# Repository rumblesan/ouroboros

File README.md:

# Ouroboros

A noisy feedback system

## Description

A pinged filter feeds a PT delay, which feeds a comparator, which feeds some clock dividers, which pings the filter and modulate the rest of the system

## Contact

Drop me an email at guy@rumblesan.com

## License

This work is licensed under a [Creative Commons Attribution 4.0 International License]("http://creativecommons.org/licenses/by/4.0/")

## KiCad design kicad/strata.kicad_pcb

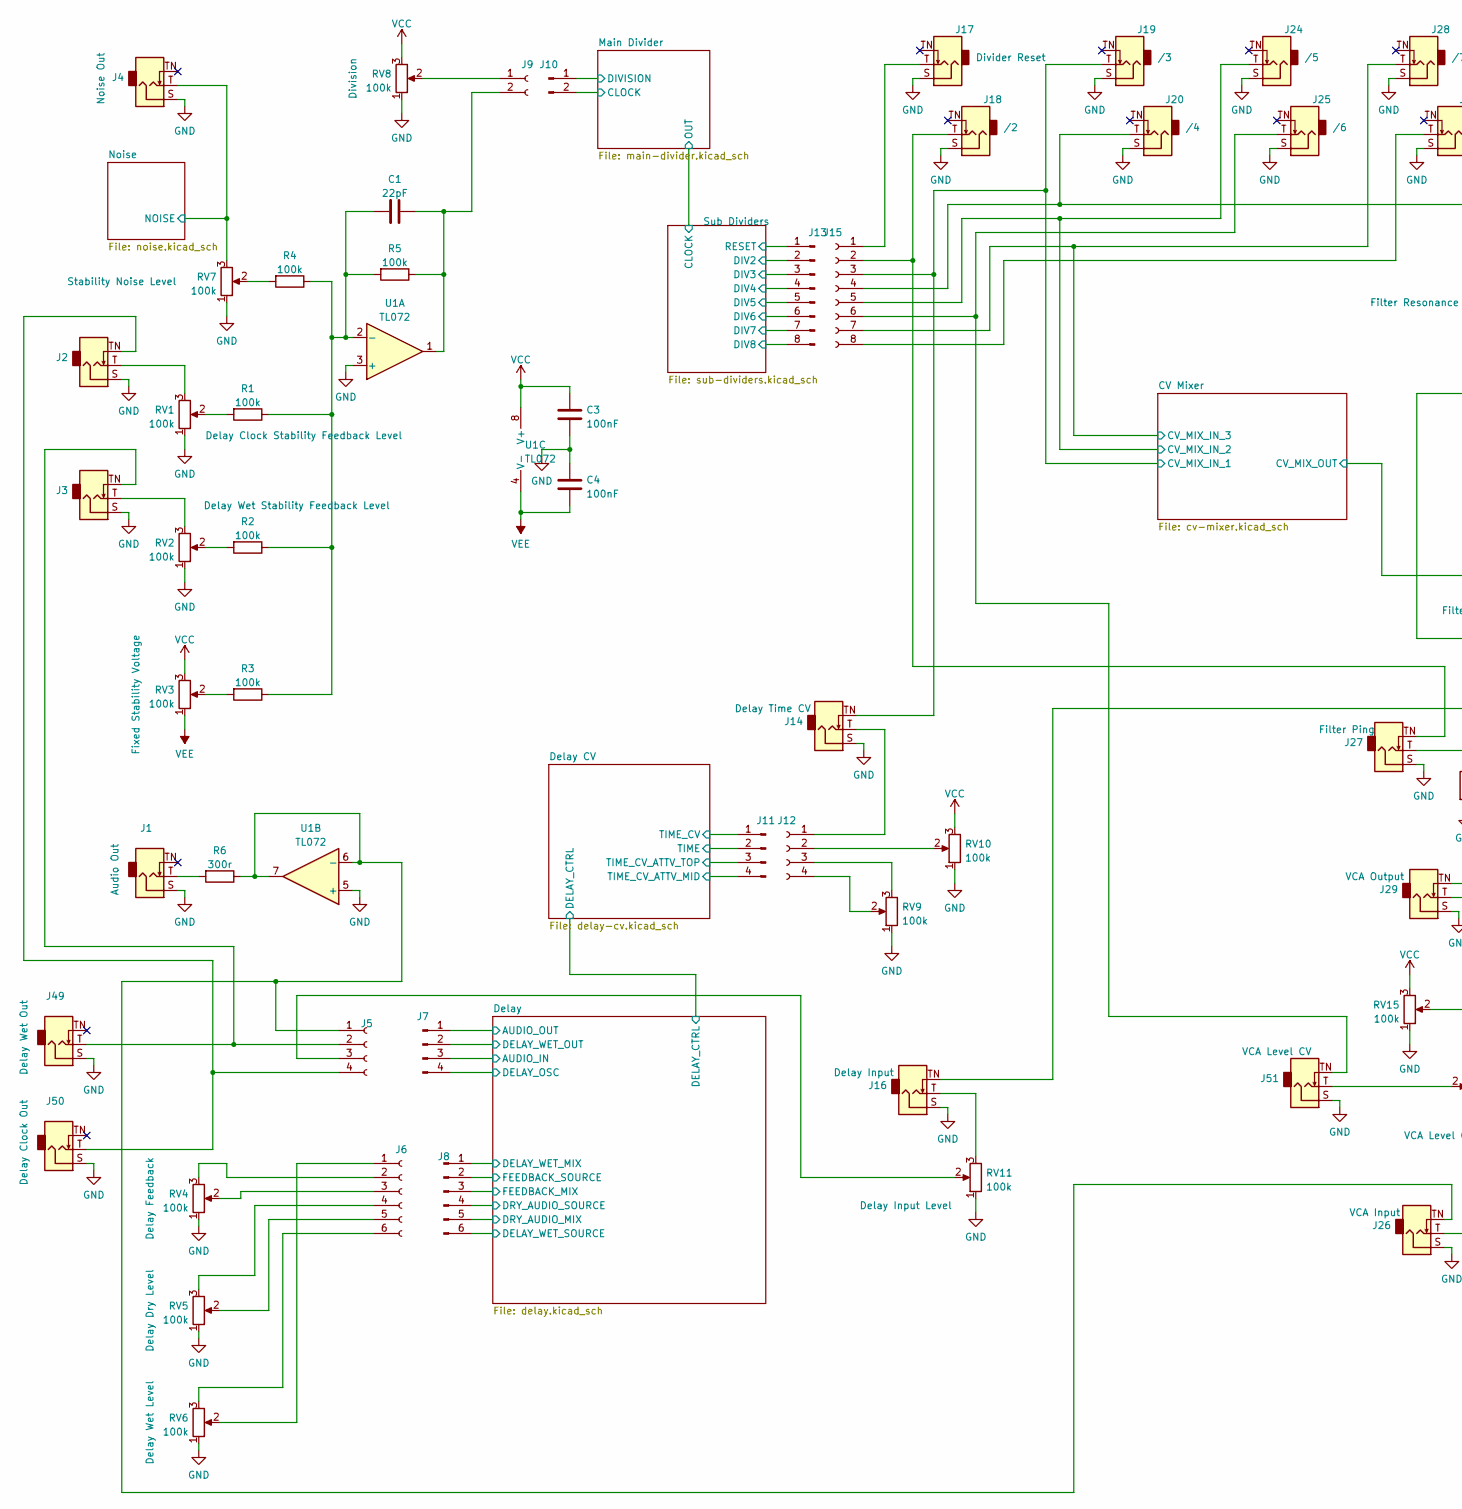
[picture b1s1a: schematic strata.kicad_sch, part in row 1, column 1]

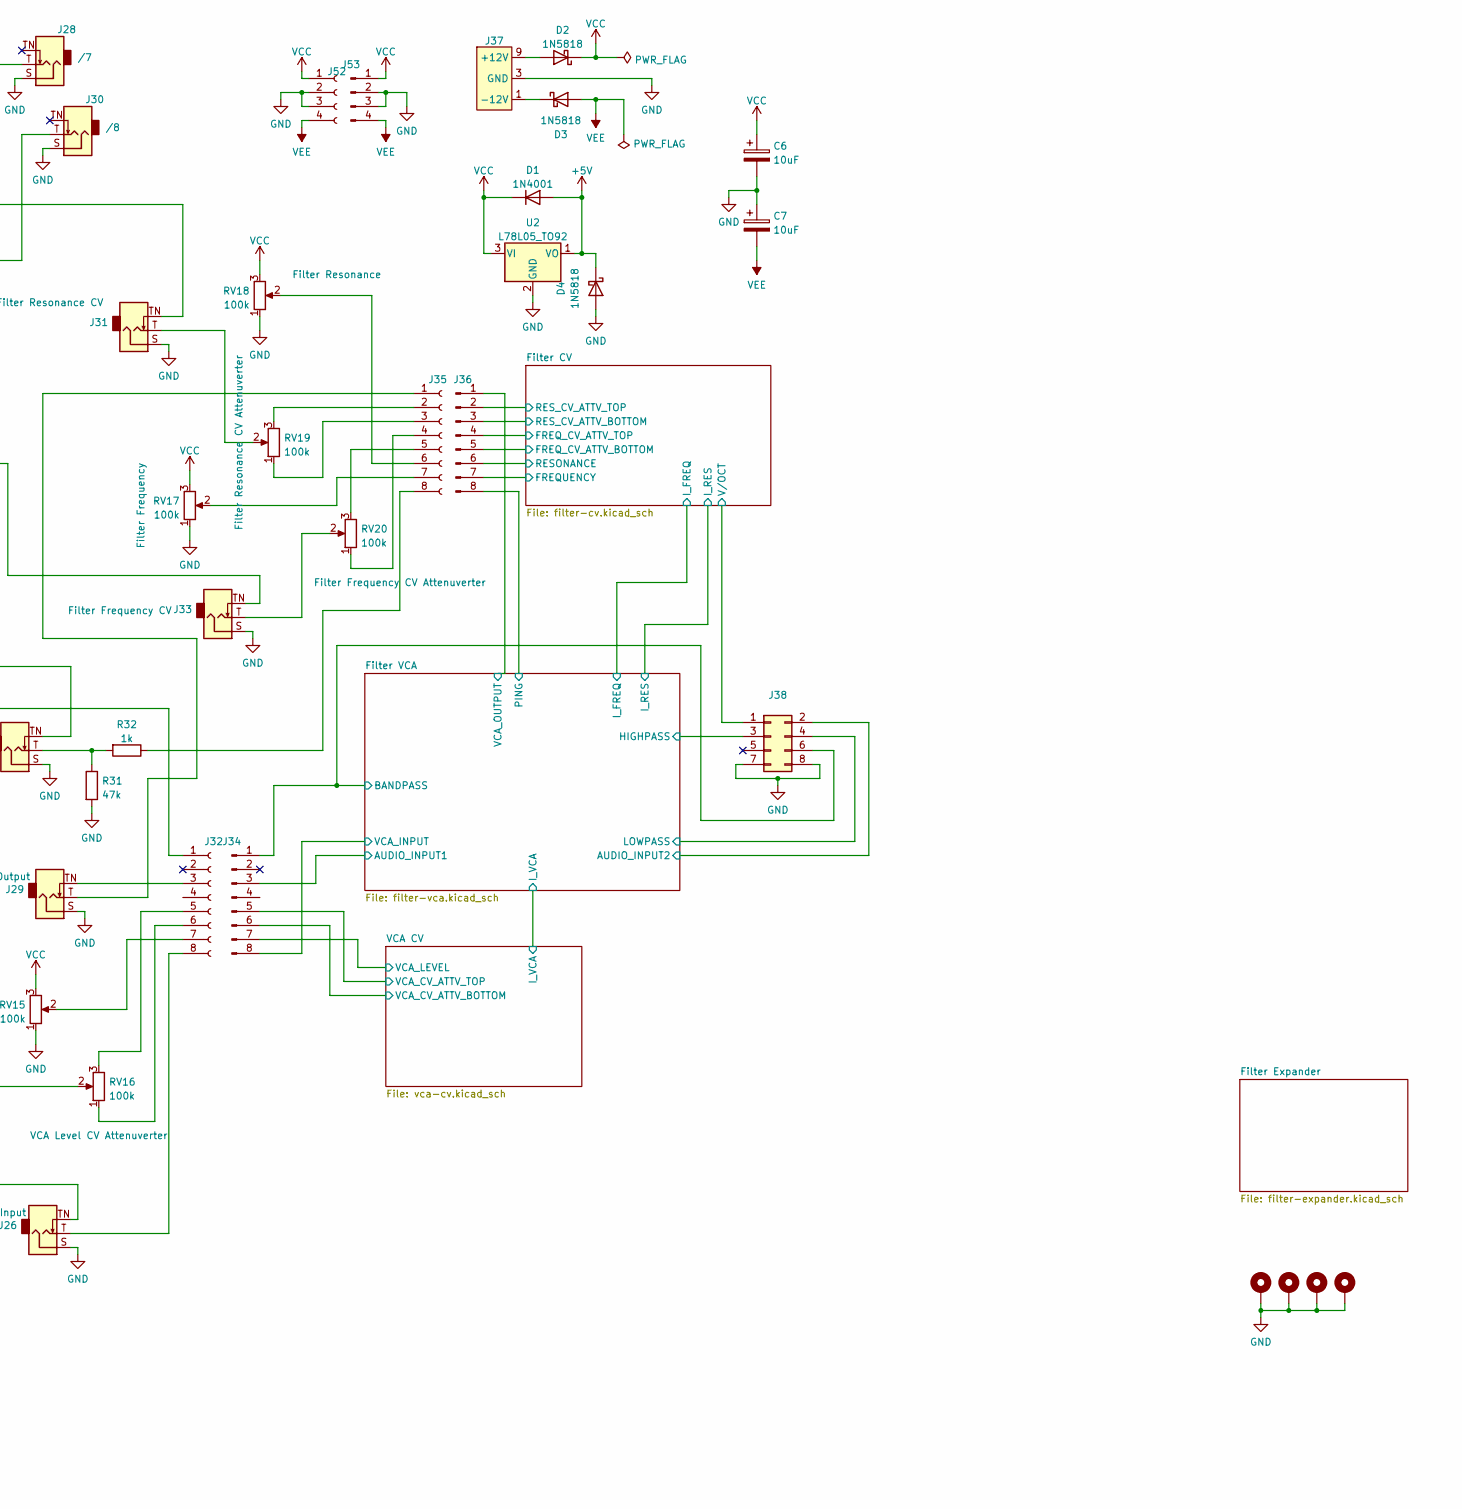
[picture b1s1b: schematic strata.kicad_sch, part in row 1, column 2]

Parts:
C1: 22pF; C_Rect_L7.0mm_W2.5mm_P5.00mm; Tolerance 5%
C3, C4: 100nF; C_Rect_L7.0mm_W2.5mm_P5.00mm; Tolerance 5%
C6, C7: 10uF; CP_Radial_D5.0mm_P2.00mm; Tolerance 20%; Voltage 50v
D1: 1N4001; D_DO-41_SOD81_P10.16mm_Horizontal
D2, D3, D4: 1N5818; D_DO-41_SOD81_P10.16mm_Horizontal
H1, H2, H3, H4: MountingHole_Pad; MountingHole_3.2mm_M3_DIN965_Pad
J1, J2, J3, J4, J14, J16, J17, J18, J19, J20, J24, J25, J26, J27, J28, J29, J30, J31, J33, J49, J50, J51: Eurorack Mono Jack; Jack_3.5mm_QingPu_WQP-PJ398SM_Vertical; mpn WQP-WQP518MA
J5, J12, J52: Conn_01x04_Female; PinSocket_1x04_P2.54mm_Vertical
J6: Conn_01x06_Female; PinSocket_1x06_P2.54mm_Vertical
J7, J11, J53: Conn_01x04_Male; PinHeader_1x04_P2.54mm_Vertical
J8: Conn_01x06_Male; PinHeader_1x06_P2.54mm_Vertical
J9: Conn_01x02_Female; PinSocket_1x02_P2.54mm_Vertical
J10: Conn_01x02_Male; PinHeader_1x02_P2.54mm_Vertical
J13, J34, J36: Conn_01x08_Male; PinHeader_1x08_P2.54mm_Vertical
J15, J32, J35: Conn_01x08_Female; PinSocket_1x08_P2.54mm_Vertical
J37: Eurorack Power Small; Eurorack_PowerHeader_2x05_P2.54mm_Shrouded
J38: Conn_02x04_Odd_Even; PinHeader_2x04_P2.54mm_Vertical
R1, R2, R3, R4, R5: 100k; R_Axial_DIN0207_L6.3mm_D2.5mm_P10.16mm_Horizontal; Tolerance 1%
R6: 300r; R_Axial_DIN0207_L6.3mm_D2.5mm_P10.16mm_Horizontal; Tolerance 1%
R31: 47k; R_Axial_DIN0207_L6.3mm_D2.5mm_P10.16mm_Horizontal; Tolerance 1%
R32: 1k; R_Axial_DIN0207_L6.3mm_D2.5mm_P10.16mm_Horizontal; Tolerance 1%
RV1, RV2, RV3, RV4, RV5, RV6, RV7, RV8, RV9, RV10, RV11, RV15, RV16, RV17, RV18, RV19, RV20: 100k; Potentiometer_Alpha_RD901F-40-00D_Single_Vertical
U1: TL072; DIP-8_W7.62mm_Socket
U2: L78L05_TO92; TO-92_Inline_Wide

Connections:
+5V: D1.2 (A), D4.1 (K), U2.1 (VO); also elsewhere on the board
/CV Mixer/CV_MIX_IN_1: J14.TN (Tip_normalize), J15.3, J19.T (Tip); also elsewhere on the board
/CV Mixer/CV_MIX_IN_2: J15.5, J24.T (Tip); also elsewhere on the board
/CV Mixer/CV_MIX_IN_3: J15.7, J28.T (Tip); also elsewhere on the board
/CV Mixer/CV_MIX_OUT: J33.TN (Tip_normalize); also elsewhere on the board
/Delay CV/TIME: J11.2; also elsewhere on the board
/Delay CV/TIME_CV: J11.1; also elsewhere on the board
/Delay CV/TIME_CV_ATTV_MID: J11.4; also elsewhere on the board
/Delay CV/TIME_CV_ATTV_TOP: J11.3; also elsewhere on the board
/Delay/AUDIO_IN: J7.3; also elsewhere on the board
/Delay/AUDIO_OUT: J7.1; also elsewhere on the board
/Delay/DELAY_OSC: J7.4; also elsewhere on the board
/Delay/DELAY_WET_MIX: J8.1; also elsewhere on the board
/Delay/DELAY_WET_OUT: J7.2; also elsewhere on the board
/Delay/DELAY_WET_SOURCE: J8.6; also elsewhere on the board
/Delay/DRY_AUDIO_MIX: J8.5; also elsewhere on the board
/Delay/DRY_AUDIO_SOURCE: J8.4; also elsewhere on the board
/Delay/FEEDBACK_MIX: J8.3; also elsewhere on the board
/Delay/FEEDBACK_SOURCE: J8.2; also elsewhere on the board
/Filter CV/FREQUENCY: J36.7; also elsewhere on the board
/Filter CV/FREQ_CV_ATTV_BOTTOM: J36.5; also elsewhere on the board
/Filter CV/FREQ_CV_ATTV_TOP: J36.4; also elsewhere on the board
/Filter CV/RESONANCE: J36.6; also elsewhere on the board
/Filter CV/RES_CV_ATTV_BOTTOM: J36.3; also elsewhere on the board
/Filter CV/RES_CV_ATTV_TOP: J36.2; also elsewhere on the board
/Filter CV/V/OCT: J38.1; also elsewhere on the board
/Filter VCA/AUDIO_INPUT1: J34.3; also elsewhere on the board
/Filter VCA/AUDIO_INPUT2: J38.2; also elsewhere on the board
/Filter VCA/BANDPASS: J34.1, J38.6; also elsewhere on the board
/Filter VCA/HIGHPASS: J38.3; also elsewhere on the board
/Filter VCA/LOWPASS: J38.4; also elsewhere on the board
/Filter VCA/PING: J36.8; also elsewhere on the board
/Filter VCA/VCA_INPUT: J34.8; also elsewhere on the board
/Filter VCA/VCA_OUTPUT: J36.1; also elsewhere on the board
/Main Divider/CLOCK: J10.2; also elsewhere on the board
/Main Divider/DIVISION: J10.1; also elsewhere on the board
/Noise/NOISE: J4.T (Tip), RV7.3; also elsewhere on the board
/Sub Dividers/DIV2: J13.2; also elsewhere on the board
/Sub Dividers/DIV3: J13.3; also elsewhere on the board
/Sub Dividers/DIV4: J13.4; also elsewhere on the board
/Sub Dividers/DIV5: J13.5; also elsewhere on the board
/Sub Dividers/DIV6: J13.6; also elsewhere on the board
/Sub Dividers/DIV7: J13.7; also elsewhere on the board
/Sub Dividers/DIV8: J13.8; also elsewhere on the board
/Sub Dividers/RESET: J13.1; also elsewhere on the board
/VCA CV/VCA_CV_ATTV_BOTTOM: J34.6; also elsewhere on the board
/VCA CV/VCA_CV_ATTV_TOP: J34.5; also elsewhere on the board
/VCA CV/VCA_LEVEL: J34.7; also elsewhere on the board
GND: C3.2, C4.1, C6.2, C7.1, D4.2 (A), H1.1, H2.1, H3.1, H4.1, J1.S (Sleeve), J2.S (Sleeve), J3.S (Sleeve), J4.S (Sleeve), J14.S (Sleeve), J16.S (Sleeve), J17.S (Sleeve), J18.S (Sleeve), J19.S (Sleeve), J20.S (Sleeve), J24.S (Sleeve), J25.S (Sleeve), J26.S (Sleeve), J27.S (Sleeve), J28.S (Sleeve), J29.S (Sleeve), J30.S (Sleeve), J31.S (Sleeve), J33.S (Sleeve), J37.3 (GND), J37.4 (GND), J37.5 (GND), J37.6 (GND), J37.7 (GND), J37.8 (GND), J38.7, J38.8, J49.S (Sleeve), J50.S (Sleeve), J51.S (Sleeve), J52.2, J52.3, J53.2, J53.3, R31.2, RV1.1, RV2.1, RV4.1, RV5.1, RV6.1, RV7.1, RV8.1, RV9.1, RV10.1, RV11.1, RV15.1, RV17.1, RV18.1, U1.3 (+), U1.5 (+), U2.2 (GND); also elsewhere on the board
unnamed: C1.1, R1.1, R2.1, R3.1, R4.1, R5.2, U1.2 (-)
unnamed: C1.2, J9.2, R5.1, U1.1
unnamed: D2.2 (A), J37.9 (+12V), J37.10 (+12V)
unnamed: D3.1 (K), J37.1 (-12V), J37.2 (-12V)
unnamed: J1.T (Tip), R6.2
unnamed: J2.T (Tip), RV1.3
unnamed: J2.TN (Tip_normalize), J5.4, J50.T (Tip)
unnamed: J3.T (Tip), RV2.3
unnamed: J3.TN (Tip_normalize), J5.2, J49.T (Tip)
unnamed: J5.3, RV11.2
unnamed: J6.1, RV6.2
unnamed: J6.4, RV5.3
unnamed: J9.1, RV8.2
unnamed: J12.1, J14.T (Tip)
unnamed: J12.2, RV10.2
unnamed: J12.3, RV9.3
unnamed: J12.4, RV9.2
unnamed: J15.1, J17.T (Tip)
unnamed: J15.2, J18.T (Tip), J27.TN (Tip_normalize)
unnamed: J15.4, J20.T (Tip), J31.TN (Tip_normalize)
unnamed: J15.6, J25.T (Tip), J51.TN (Tip_normalize)
unnamed: J15.8, J30.T (Tip)
unnamed: J16.T (Tip), RV11.3
unnamed: J16.TN (Tip_normalize), J32.1
unnamed: J26.T (Tip), J32.8
unnamed: J5.1, J26.TN (Tip_normalize), R6.1, U1.6 (-), U1.7
unnamed: J27.T (Tip), R31.1, R32.2
unnamed: J29.T (Tip), J35.1
unnamed: J29.TN (Tip_normalize), J32.3
unnamed: J31.T (Tip), RV19.2
unnamed: J32.5, RV16.3
unnamed: J32.6, RV16.1
unnamed: J32.7, RV15.2
unnamed: J33.T (Tip), RV20.2
unnamed: J35.2, RV19.3
unnamed: J35.3, RV19.1
unnamed: J35.4, RV20.1
unnamed: J35.5, RV20.3
unnamed: J35.6, RV18.2
unnamed: J35.7, RV17.2
unnamed: J35.8, R32.1
unnamed: J51.T (Tip), RV16.2
unnamed: R1.2, RV1.2
unnamed: R2.2, RV2.2
unnamed: R3.2, RV3.2
unnamed: R4.2, RV7.2
unnamed: J6.3, RV4.2
unnamed: J6.2, RV4.3
unnamed: J6.5, RV5.2
unnamed: J6.6, RV6.3
VCC: C3.1, C6.1, D1.1 (K), D2.1 (K), J52.1, J53.1, RV3.3, RV8.3, RV10.3, RV15.3, RV17.3, RV18.3, U1.8 (V+), U2.3 (VI); also elsewhere on the board
VEE: C4.2, C7.2, D3.2 (A), J52.4, J53.4, RV3.1, U1.4 (V-); also elsewhere on the board

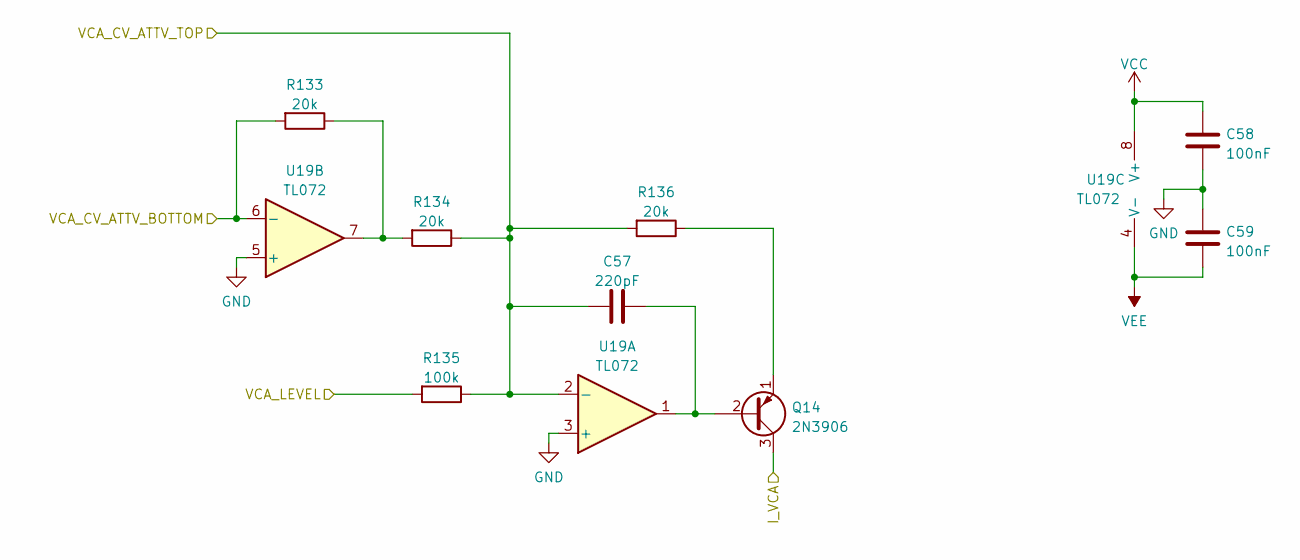
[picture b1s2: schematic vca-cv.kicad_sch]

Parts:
C57: 220pF; C_Rect_L7.0mm_W2.5mm_P5.00mm; Tolerance 5%
C58, C59: 100nF; C_Rect_L7.0mm_W2.5mm_P5.00mm; Tolerance 5%
Q14: 2N3906; TO-92_Inline_Wide
R133, R134, R136: 20k; R_Axial_DIN0207_L6.3mm_D2.5mm_P10.16mm_Horizontal; Tolerance 1%
R135: 100k; R_Axial_DIN0207_L6.3mm_D2.5mm_P10.16mm_Horizontal; Tolerance 1%
U19: TL072; DIP-8_W7.62mm_Socket

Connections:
/Filter VCA/I_VCA: Q14.3 (C); also elsewhere on the board
/VCA CV/VCA_CV_ATTV_BOTTOM: R133.2, U19.6 (-); also elsewhere on the board
/VCA CV/VCA_CV_ATTV_TOP: C57.1, R134.1, R135.1, R136.2, U19.2 (-); also elsewhere on the board
/VCA CV/VCA_LEVEL: R135.2; also elsewhere on the board
GND: C58.2, C59.1, U19.3 (+), U19.5 (+); also elsewhere on the board
unnamed: C57.2, Q14.2 (B), U19.1
unnamed: Q14.1 (E), R136.1
unnamed: R133.1, R134.2, U19.7
VCC: C58.1, U19.8 (V+); also elsewhere on the board
VEE: C59.2, U19.4 (V-); also elsewhere on the board

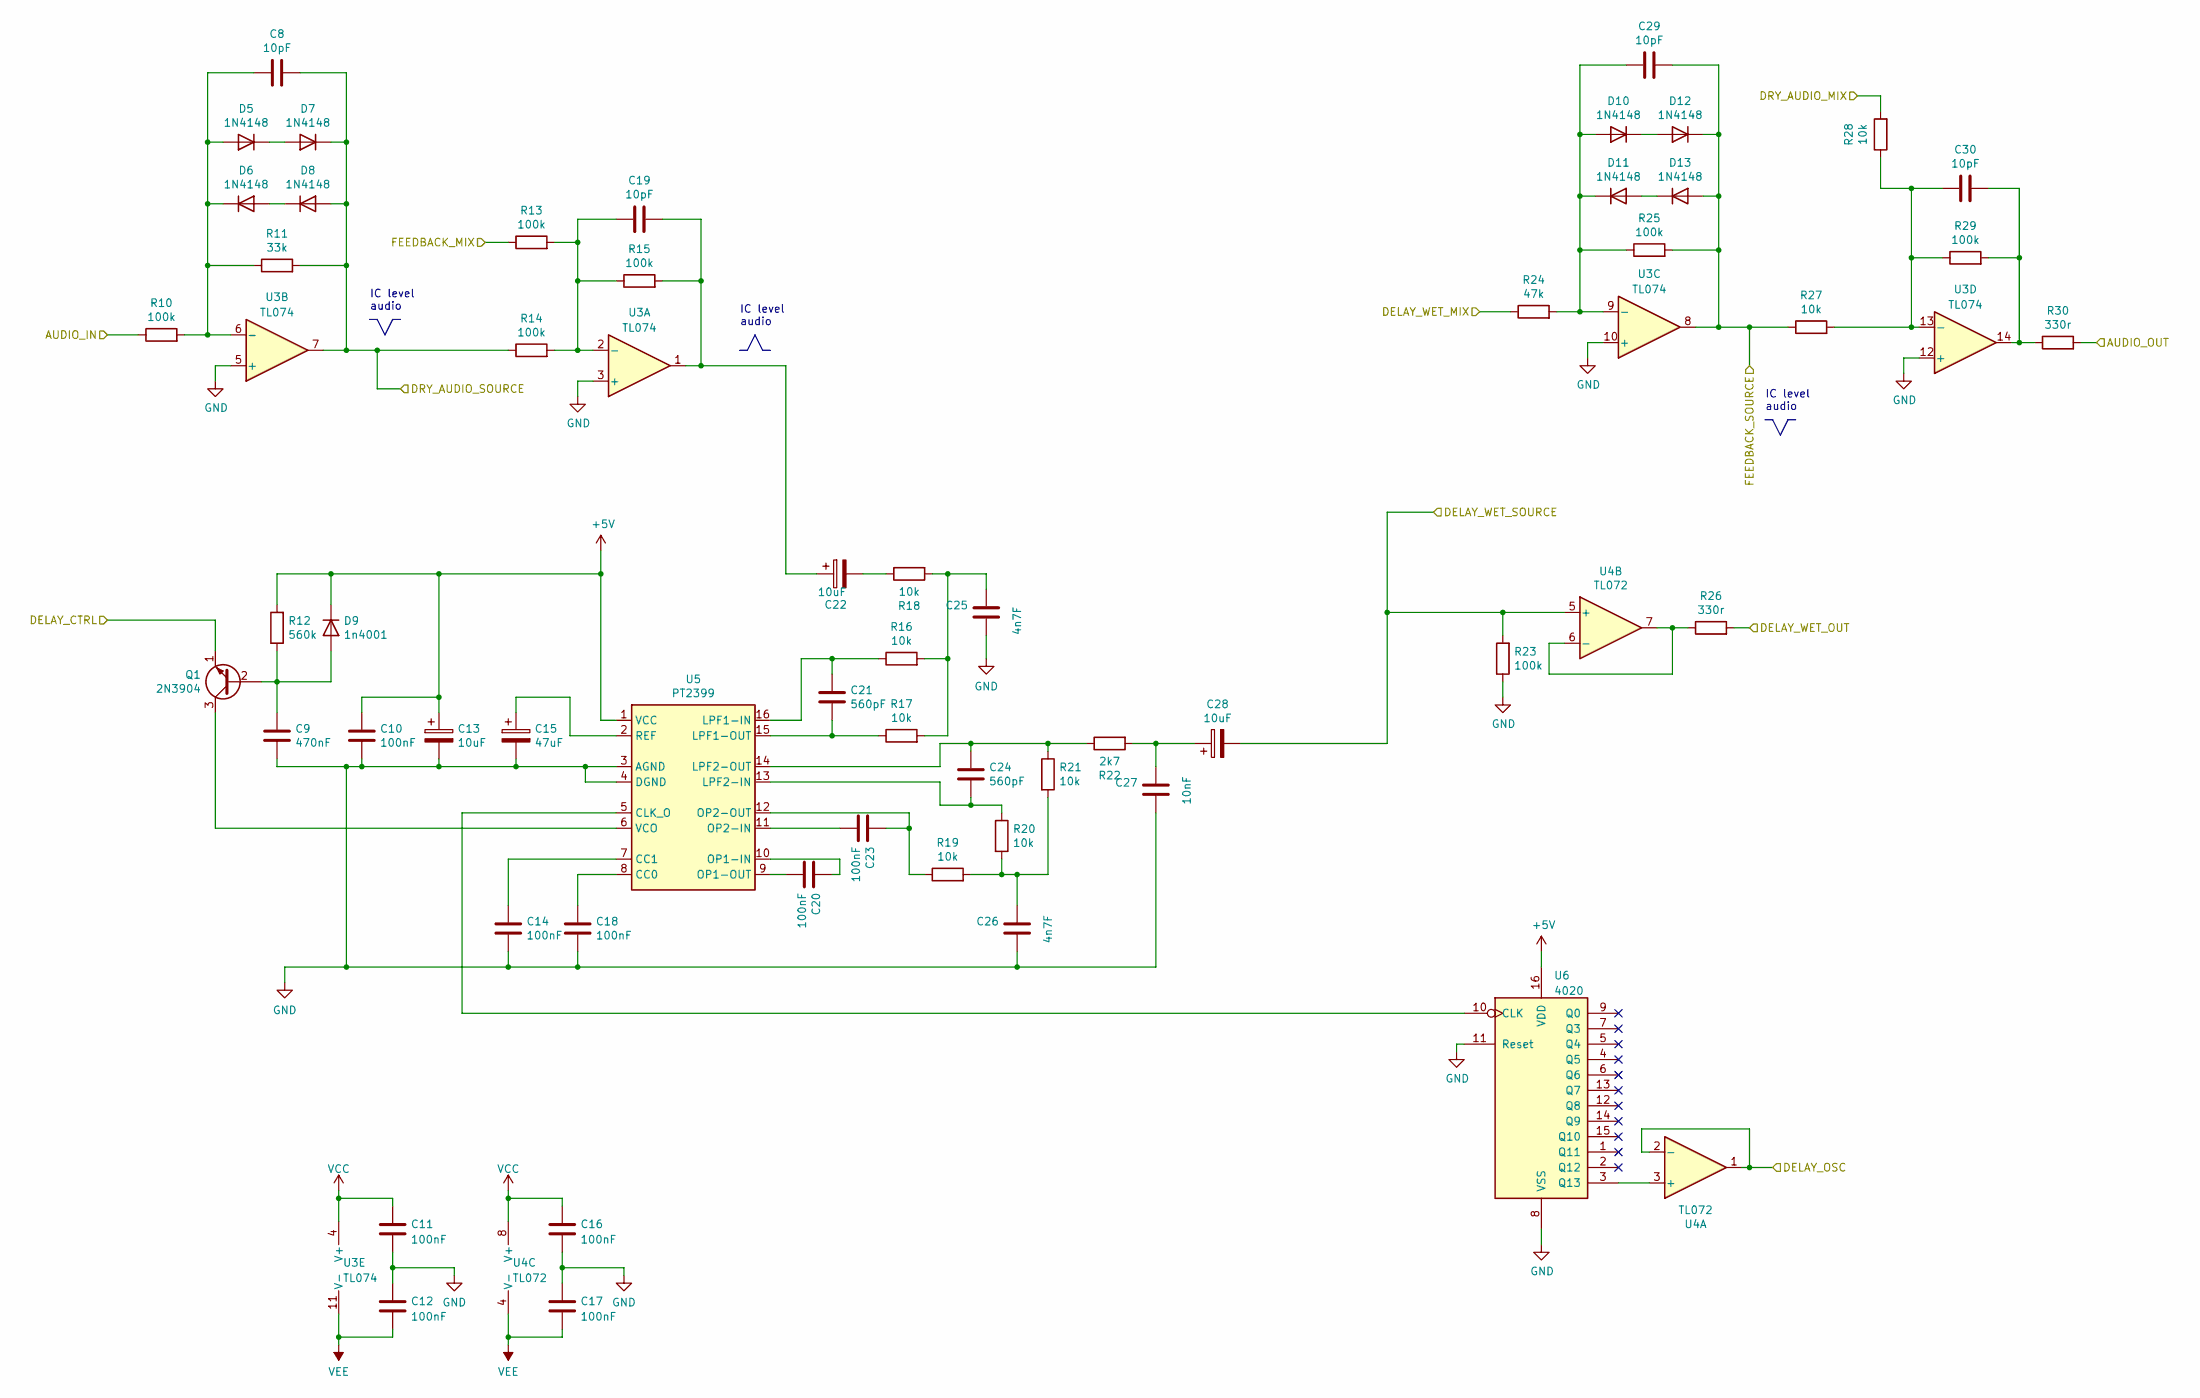
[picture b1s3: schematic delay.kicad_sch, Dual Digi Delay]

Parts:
C8, C19, C29, C30: 10pF; C_Rect_L7.0mm_W2.5mm_P5.00mm; Tolerance 5%
C9: 470nF; C_Rect_L7.0mm_W3.5mm_P5.00mm; Tolerance 5%
C10, C11, C12, C16, C17: 100nF; C_Rect_L7.0mm_W2.5mm_P5.00mm; Tolerance 5%
C13, C22, C28: 10uF; CP_Radial_D5.0mm_P2.00mm; Tolerance 20%; Voltage 50v
C14, C18, C20, C23: 100nF; C_Rect_L7.0mm_W3.5mm_P5.00mm; Tolerance 5%
C15: 47uF; CP_Radial_D6.3mm_P2.50mm; Tolerance 20%; Voltage 50v
C21, C24: 560pF; C_Rect_L7.0mm_W3.5mm_P5.00mm; Tolerance 5%
C25, C26: 4n7F; C_Rect_L7.0mm_W3.5mm_P5.00mm; Tolerance 5%
C27: 10nF; C_Rect_L7.0mm_W3.5mm_P5.00mm; Tolerance 5%
D5, D6, D7, D8, D10, D11, D12, D13: 1N4148; D_DO-35_SOD27_P7.62mm_Horizontal
D9: 1n4001; D_DO-41_SOD81_P10.16mm_Horizontal
Q1: 2N3904; TO-92_Inline_Wide
R10, R13, R14, R15, R23, R25, R29: 100k; R_Axial_DIN0207_L6.3mm_D2.5mm_P10.16mm_Horizontal; Tolerance 1%
R11: 33k; R_Axial_DIN0207_L6.3mm_D2.5mm_P10.16mm_Horizontal; Tolerance 1%
R12: 560k; R_Axial_DIN0207_L6.3mm_D2.5mm_P10.16mm_Horizontal; Tolerance 1%
R16, R17, R18, R19, R20, R21, R27, R28: 10k; R_Axial_DIN0207_L6.3mm_D2.5mm_P10.16mm_Horizontal; Tolerance 1%
R22: 2k7; R_Axial_DIN0207_L6.3mm_D2.5mm_P10.16mm_Horizontal; Tolerance 1%
R24: 47k; R_Axial_DIN0207_L6.3mm_D2.5mm_P10.16mm_Horizontal; Tolerance 1%
R26, R30: 330r; R_Axial_DIN0207_L6.3mm_D2.5mm_P10.16mm_Horizontal; Tolerance 1%
U3: TL074; DIP-14_W7.62mm_Socket
U4: TL072; DIP-8_W7.62mm_Socket
U5: PT2399; DIP-16_W7.62mm_Socket
U6: 4020; DIP-16_W7.62mm_Socket

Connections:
+5V: C10.2, C13.1, D9.1 (K), R12.2, U5.1 (VCC), U6.16 (VDD); also elsewhere on the board
/Delay CV/DELAY_CTRL: Q1.1 (E); also elsewhere on the board
/Delay/AUDIO_IN: R10.1; also elsewhere on the board
/Delay/AUDIO_OUT: R30.2; also elsewhere on the board
/Delay/DELAY_OSC: U4.1, U4.2 (-); also elsewhere on the board
/Delay/DELAY_WET_MIX: R24.1; also elsewhere on the board
/Delay/DELAY_WET_OUT: R26.2; also elsewhere on the board
/Delay/DELAY_WET_SOURCE: C28.2, R23.2, U4.5 (+); also elsewhere on the board
/Delay/DRY_AUDIO_MIX: R28.2; also elsewhere on the board
/Delay/DRY_AUDIO_SOURCE: C8.1, D7.1 (K), D8.2 (A), R11.2, R14.1, U3.7; also elsewhere on the board
/Delay/FEEDBACK_MIX: R13.1; also elsewhere on the board
/Delay/FEEDBACK_SOURCE: C29.1, D12.1 (K), D13.2 (A), R25.2, R27.1, U3.8; also elsewhere on the board
GND: C9.2, C10.1, C11.2, C12.1, C13.2, C14.1, C15.2, C16.2, C17.1, C18.1, C25.1, C26.1, C27.1, R23.1, U3.3 (+), U3.5 (+), U3.10 (+), U3.12 (+), U5.3 (AGND), U5.4 (DGND), U6.8 (VSS), U6.11 (Reset); also elsewhere on the board
unnamed: C8.2, D5.2 (A), D6.1 (K), R10.2, R11.1, U3.6 (-)
unnamed: C9.1, D9.2 (A), Q1.2 (B), R12.1
unnamed: C14.2, U5.7 (CC1)
unnamed: C15.1, U5.2 (REF)
unnamed: C18.2, U5.8 (CC0)
unnamed: C19.1, C22.1, R15.2, U3.1
unnamed: C19.2, R13.2, R14.2, R15.1, U3.2 (-)
unnamed: C20.1, U5.9 (OP1-OUT)
unnamed: C20.2, U5.10 (OP1-IN)
unnamed: C21.1, R17.1, U5.15 (LPF1-OUT)
unnamed: C21.2, R16.1, U5.16 (LPF1-IN)
unnamed: C22.2, R18.1
unnamed: C23.1, U5.11 (OP2-IN)
unnamed: C23.2, R19.1, U5.12 (OP2-OUT)
unnamed: C24.1, R21.1, R22.1, U5.14 (LPF2-OUT)
unnamed: C24.2, R20.1, U5.13 (LPF2-IN)
unnamed: C25.2, R16.2, R17.2, R18.2
unnamed: C26.2, R19.2, R20.2, R21.2
unnamed: C27.2, C28.1, R22.2
unnamed: C29.2, D10.2 (A), D11.1 (K), R24.2, R25.1, U3.9 (-)
unnamed: C30.1, R29.2, R30.1, U3.14
unnamed: C30.2, R27.2, R28.1, R29.1, U3.13 (-)
unnamed: D5.1 (K), D7.2 (A)
unnamed: D6.2 (A), D8.1 (K)
unnamed: D10.1 (K), D12.2 (A)
unnamed: D11.2 (A), D13.1 (K)
unnamed: Q1.3 (C), U5.6 (VCO)
unnamed: R26.1, U4.6 (-), U4.7
unnamed: U4.3 (+), U6.3 (Q13)
unnamed: U5.5 (CLK_O), U6.10 (CLK)
VCC: C11.1, C16.1, U3.4 (V+), U4.8 (V+); also elsewhere on the board
VEE: C12.2, C17.2, U3.11 (V-), U4.4 (V-); also elsewhere on the board

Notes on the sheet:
IC level audio

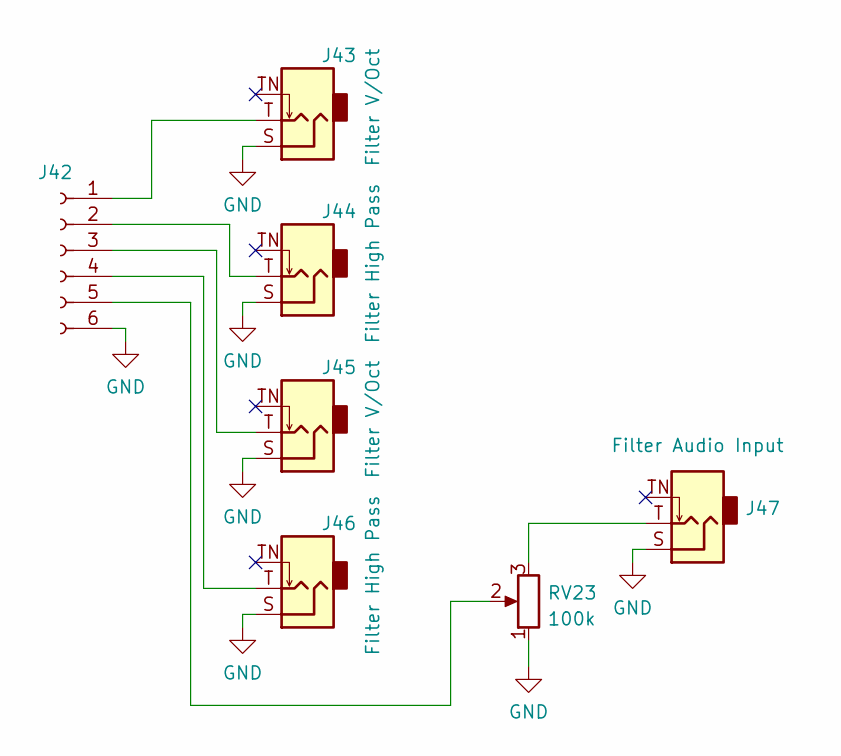
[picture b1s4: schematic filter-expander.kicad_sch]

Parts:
J42: Conn_01x06_Female; PinSocket_1x06_P2.54mm_Vertical
J43, J44, J45, J46, J47: Eurorack Mono Jack; Jack_3.5mm_QingPu_WQP-PJ398SM_Vertical; mpn WQP-WQP518MA
RV23: 100k; Potentiometer_Alpha_RD901F-40-00D_Single_Vertical

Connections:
GND: J42.6, J43.S (Sleeve), J44.S (Sleeve), J45.S (Sleeve), J46.S (Sleeve), J47.S (Sleeve), RV23.1; also elsewhere on the board
unnamed: J42.1, J43.T (Tip)
unnamed: J42.2, J44.T (Tip)
unnamed: J42.3, J45.T (Tip)
unnamed: J42.4, J46.T (Tip)
unnamed: J42.5, RV23.2
unnamed: J47.T (Tip), RV23.3

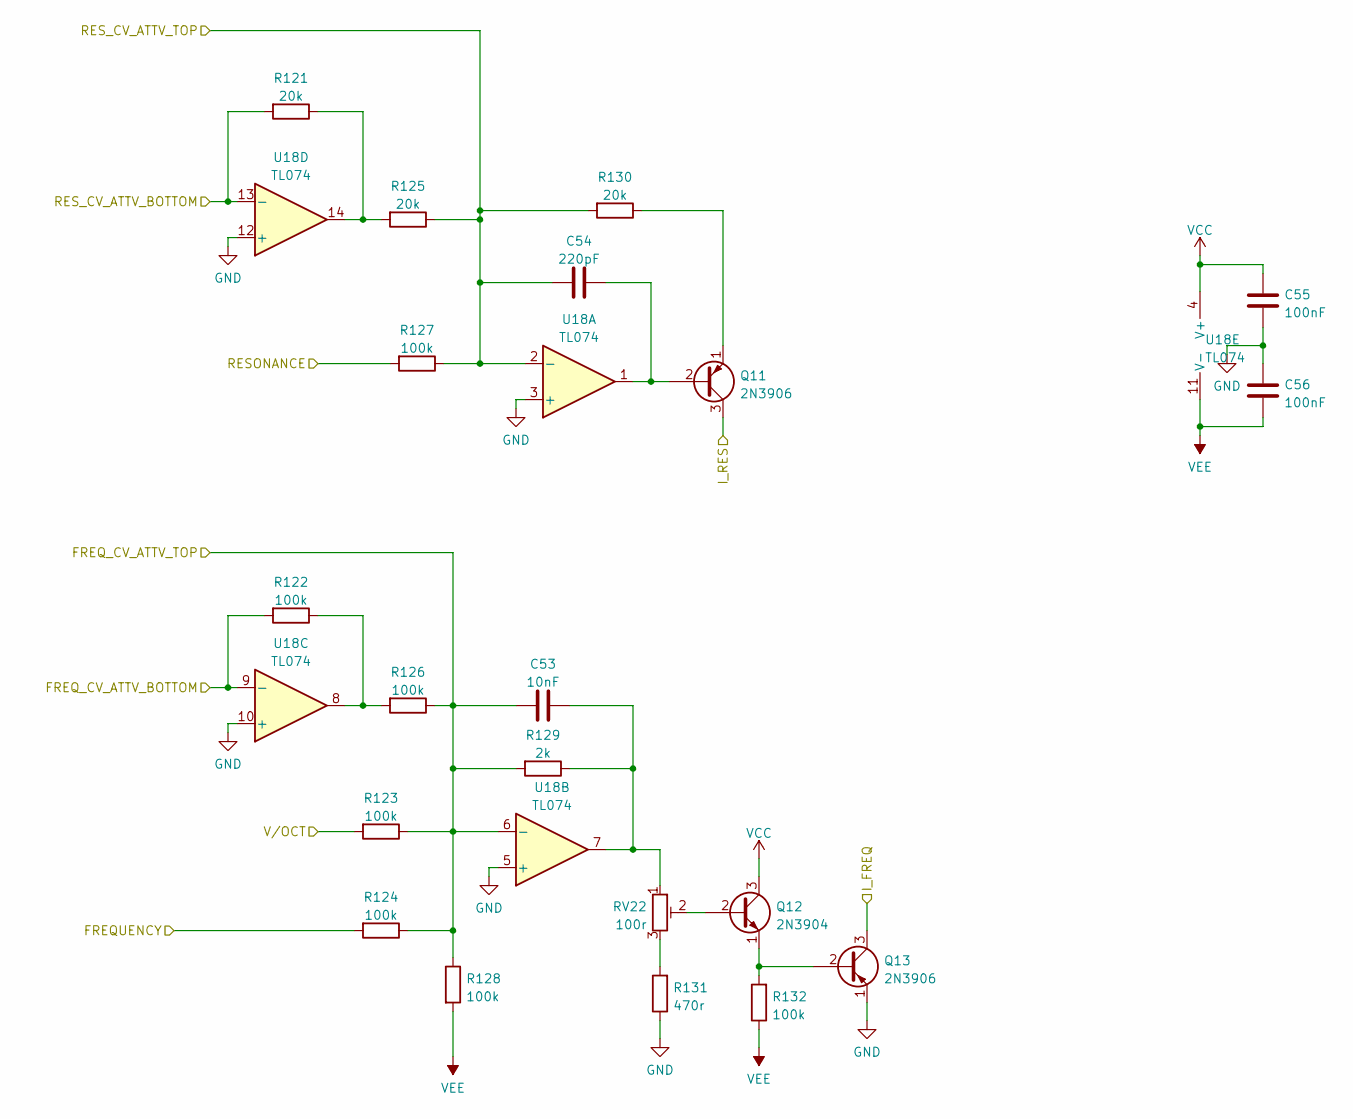
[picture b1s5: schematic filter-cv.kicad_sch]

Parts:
C53: 10nF; C_Rect_L7.0mm_W3.5mm_P5.00mm; Tolerance 5%
C54: 220pF; C_Rect_L7.0mm_W3.5mm_P5.00mm; Tolerance 5%
C55, C56: 100nF; C_Rect_L7.0mm_W2.5mm_P5.00mm; Tolerance 5%
Q11, Q13: 2N3906; TO-92_Inline_Wide
Q12: 2N3904; TO-92_Inline_Wide
R121, R125, R130: 20k; R_Axial_DIN0207_L6.3mm_D2.5mm_P10.16mm_Horizontal; Tolerance 1%
R122, R123, R124, R126, R127, R128, R132: 100k; R_Axial_DIN0207_L6.3mm_D2.5mm_P10.16mm_Horizontal; Tolerance 1%
R129: 2k; R_Axial_DIN0207_L6.3mm_D2.5mm_P10.16mm_Horizontal; Tolerance 1%
R131: 470r; R_Axial_DIN0207_L6.3mm_D2.5mm_P10.16mm_Horizontal; Tolerance 1%
RV22: 100r; Potentiometer_THT_Bourns_3306P_Vertical
U18: TL074; DIP-14_W7.62mm_Socket

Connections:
/Filter CV/FREQUENCY: R124.2; also elsewhere on the board
/Filter CV/FREQ_CV_ATTV_BOTTOM: R122.2, U18.9 (-); also elsewhere on the board
/Filter CV/FREQ_CV_ATTV_TOP: C53.1, R123.1, R124.1, R126.1, R128.1, R129.2, U18.6 (-); also elsewhere on the board
/Filter CV/I_FREQ: Q13.3 (C); also elsewhere on the board
/Filter CV/I_RES: Q11.3 (C); also elsewhere on the board
/Filter CV/RESONANCE: R127.2; also elsewhere on the board
/Filter CV/RES_CV_ATTV_BOTTOM: R121.2, U18.13 (-); also elsewhere on the board
/Filter CV/RES_CV_ATTV_TOP: C54.1, R125.1, R127.1, R130.2, U18.2 (-); also elsewhere on the board
/Filter CV/V/OCT: R123.2; also elsewhere on the board
GND: C55.2, C56.1, Q13.1 (E), R131.1, U18.3 (+), U18.5 (+), U18.10 (+), U18.12 (+); also elsewhere on the board
unnamed: C53.2, R129.1, RV22.1, U18.7
unnamed: C54.2, Q11.2 (B), U18.1
unnamed: Q11.1 (E), R130.1
unnamed: Q12.1 (E), Q13.2 (B), R132.2
unnamed: Q12.2 (B), RV22.2
unnamed: R121.1, R125.2, U18.14
unnamed: R122.1, R126.2, U18.8
unnamed: R131.2, RV22.3
VCC: C55.1, Q12.3 (C), U18.4 (V+); also elsewhere on the board
VEE: C56.2, R128.2, R132.1, U18.11 (V-); also elsewhere on the board

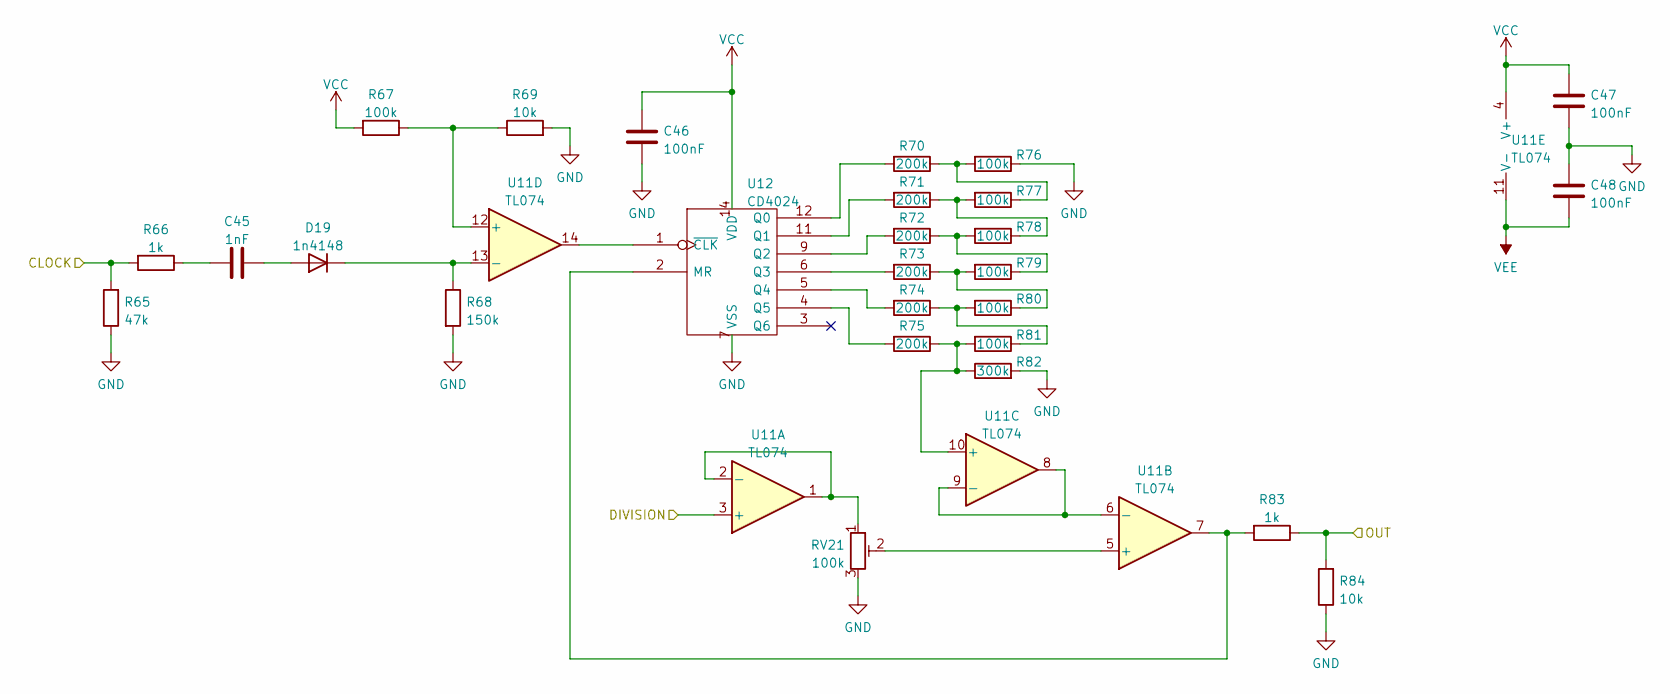
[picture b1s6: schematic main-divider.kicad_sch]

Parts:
C45: 1nF; C_Rect_L7.0mm_W3.5mm_P5.00mm; Tolerance 5%
C46, C47, C48: 100nF; C_Rect_L7.0mm_W2.5mm_P5.00mm; Tolerance 5%
D19: 1n4148; D_DO-35_SOD27_P7.62mm_Horizontal
R65: 47k; R_Axial_DIN0207_L6.3mm_D2.5mm_P10.16mm_Horizontal; Tolerance 1%
R66, R83: 1k; R_Axial_DIN0207_L6.3mm_D2.5mm_P10.16mm_Horizontal; Tolerance 1%
R67, R76, R77, R78, R79, R80, R81: 100k; R_Axial_DIN0207_L6.3mm_D2.5mm_P10.16mm_Horizontal; Tolerance 1%
R68: 150k; R_Axial_DIN0207_L6.3mm_D2.5mm_P10.16mm_Horizontal; Tolerance 1%
R69, R84: 10k; R_Axial_DIN0207_L6.3mm_D2.5mm_P10.16mm_Horizontal; Tolerance 1%
R70, R71, R72, R73, R74, R75: 200k; R_Axial_DIN0207_L6.3mm_D2.5mm_P10.16mm_Horizontal; Tolerance 1%
R82: 300k; R_Axial_DIN0207_L6.3mm_D2.5mm_P10.16mm_Horizontal; Tolerance 1%
RV21: 100k; Potentiometer_THT_Bourns_3306P_Vertical
U11: TL074; DIP-14_W7.62mm_Socket
U12: CD4024; DIP-14_W7.62mm_Socket

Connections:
/Main Divider/CLOCK: R65.2, R66.2; also elsewhere on the board
/Main Divider/DIVISION: U11.3 (+); also elsewhere on the board
/Main Divider/OUT: R83.1, R84.2; also elsewhere on the board
GND: C46.2, C47.2, C48.1, R65.1, R68.2, R69.2, R76.1, R82.2, R84.1, RV21.3, U12.7 (VSS); also elsewhere on the board
unnamed: C45.1, R66.1
unnamed: C45.2, D19.2 (A)
unnamed: D19.1 (K), R68.1, U11.13 (-)
unnamed: R67.1, R69.1, U11.12 (+)
unnamed: R70.1, R76.2, R77.1
unnamed: R70.2, U12.12 (Q0)
unnamed: R71.1, R77.2, R78.1
unnamed: R71.2, U12.11 (Q1)
unnamed: R72.1, R78.2, R79.1
unnamed: R72.2, U12.9 (Q2)
unnamed: R73.1, R79.2, R80.1
unnamed: R73.2, U12.6 (Q3)
unnamed: R74.1, R80.2, R81.1
unnamed: R74.2, U12.5 (Q4)
unnamed: R75.1, R81.2, R82.1, U11.10 (+)
unnamed: R75.2, U12.4 (Q5)
unnamed: R83.2, U11.7, U12.2 (MR)
unnamed: RV21.1, U11.1, U11.2 (-)
unnamed: RV21.2, U11.5 (+)
unnamed: U11.6 (-), U11.8, U11.9 (-)
unnamed: U11.14, U12.1 (~CLK)
VCC: C46.1, C47.1, R67.2, U11.4 (V+), U12.14 (VDD); also elsewhere on the board
VEE: C48.2, U11.11 (V-); also elsewhere on the board

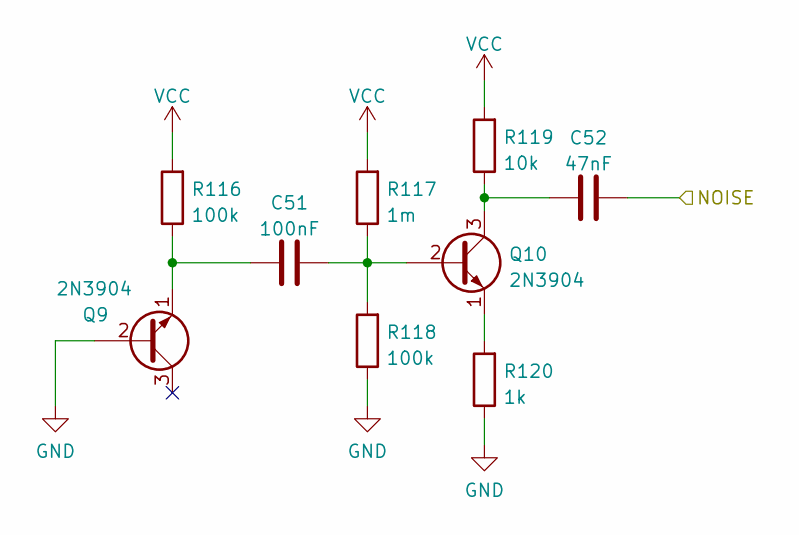
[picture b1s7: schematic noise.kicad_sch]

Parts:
C51: 100nF; C_Rect_L7.0mm_W2.5mm_P5.00mm; Tolerance 5%
C52: 47nF; C_Rect_L7.0mm_W3.5mm_P5.00mm; Tolerance 5%
Q9, Q10: 2N3904; TO-92_Inline_Wide
R116, R118: 100k; R_Axial_DIN0207_L6.3mm_D2.5mm_P10.16mm_Horizontal; Tolerance 1%
R117: 1m; R_Axial_DIN0207_L6.3mm_D2.5mm_P10.16mm_Horizontal; Tolerance 1%
R119: 10k; R_Axial_DIN0207_L6.3mm_D2.5mm_P10.16mm_Horizontal; Tolerance 1%
R120: 1k; R_Axial_DIN0207_L6.3mm_D2.5mm_P10.16mm_Horizontal; Tolerance 1%

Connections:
/Noise/NOISE: C52.2; also elsewhere on the board
GND: Q9.2 (B), R118.1, R120.1; also elsewhere on the board
unnamed: C51.1, Q9.1 (E), R116.1
unnamed: C51.2, Q10.2 (B), R117.1, R118.2
unnamed: C52.1, Q10.3 (C), R119.1
unnamed: Q10.1 (E), R120.2
VCC: R116.2, R117.2, R119.2; also elsewhere on the board

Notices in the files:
kicad/delay-cv.kicad_sch:
License: CC BY 4.0
